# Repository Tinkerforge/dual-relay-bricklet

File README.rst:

Dual Relay Bricklet
===================

This repository contains the firmware source code and the hardware design
files. The documentation generator configs can be found at
https://github.com/Tinkerforge/generators

Repository Content
------------------

software/:
 * examples/: Examples for all supported languages
 * build/: Compiled files
 * src/: Source code of firmware
 * Makefile: Makefile to build project

hardware/:
 * Contains KiCad project files and additionally schematics as PDF

datasheets/:
 * Contains datasheets for sensors and complex ICs that are used

Hardware
--------

The hardware is designed with the open source EDA Suite KiCad
(http://www.kicad.org). Before you are able to open the files,
you have to install the Tinkerforge kicad-libraries
(https://github.com/Tinkerforge/kicad-libraries). You can either clone
them directly in hardware/ or clone them in a separate folder and
symlink them into hardware/
(ln -s kicad_path/kicad-libraries project_path/hardware). After that you
can open the .pro file in hardware/ with KiCad and from there view and
modify the schematics and the PCB layout.

Software
--------

If you want to do your own Brick/Bricklet firmware development we highly
recommend that you use our build environment setup script and read the
tutorial (https://www.tinkerforge.com/en/doc/Tutorials/Tutorial_Build_Environment/Tutorial.html).

To compile the C code we recommend you to install the newest GNU Arm Embedded
Toolchain (https://launchpad.net/gcc-arm-embedded/+download).
You also need to install bricklib (https://github.com/Tinkerforge/bricklib)
and brickletlib (https://github.com/Tinkerforge/brickletlib).

You can either clone it directly in software/src/ or clone it in a
separate folder and symlink it into software/src/
(ln -s bricklib_path/bricklib project_path/software/src/ and
ln -s brickletlib_path/brickletlib project_path/software/src/).
Finally make sure to have CMake installed
(http://www.cmake.org/cmake/resources/software.html).

After that you can build the firmware by invoking make in software/.
The firmware (.bin) can then be found in software/build/ and uploaded
with brickv (click button "Flashing" on start screen).

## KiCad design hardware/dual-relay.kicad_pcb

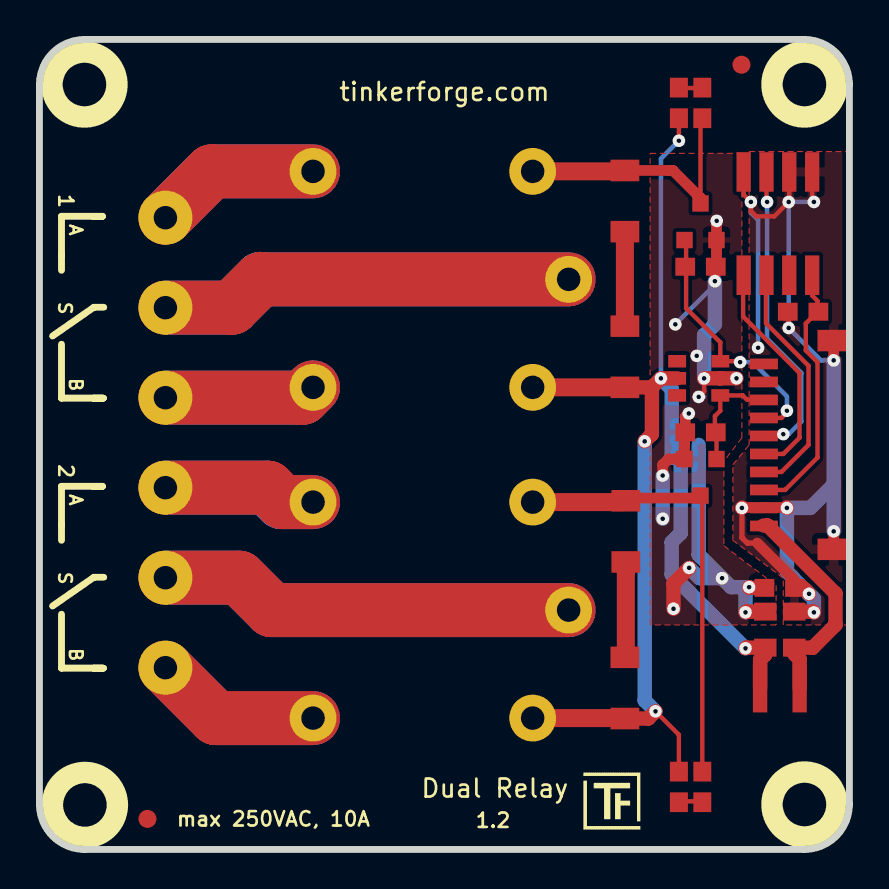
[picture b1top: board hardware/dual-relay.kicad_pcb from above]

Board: 2 copper layers, 45.0 x 45.0 mm, 34 parts (0 on the bottom side), 22 nets.

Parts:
C1, C3: 1µF; C0805
C2: 100nF; C0603E
D1, D2: LED blue; D0603E
D3, D5: 12V; MiniMelf
D4, D6: LL4148; MiniMelf
FB1: 4.7µH; NRH3015
FB2: 0R; C0603E
Fiducial_Mark: VAL**; Fiducial_Mark
Fiducial_Mark#2: VAL**; Fiducial_Mark
J1, J2, J3: AKL_5_2
P1: CON-SENSOR
Q1, Q2: 2N7002P; SOT23GDS
R1, R2, R3, R4: 1k; R0603E
Ref**: Val**; Logo_31x31
U1: M24C64; SO-8
U2, U3: ORWH-SX
U4: CM1293A; SC-74
U5, U6, U7, U8: DRILL; DRILL_NP
VAL: CE_5mm
VAL#2: WEEE_7mm

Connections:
+5V: C3.2, D1.1, D2.1, D3.1, D5.1, FB1.2, U2.1, U3.1, U4.5
AGND: C3.1, FB2.2, Q1.S, Q2.S, R1.1, R2.1, U4.2
GND: C1.1, C2.2, FB2.1, P1.2, P1.EP, U1.1, U1.2, U1.4
unnamed: C1.2, FB1.1, P1.1
unnamed: D1.2, R3.1
unnamed: D2.2, R4.1
unnamed: D3.2, D4.2
unnamed: D4.1, Q1.D, R3.2, U2.3
unnamed: D5.2, D6.2
unnamed: D6.1, Q2.D, R4.2, U3.3
unnamed: J1.1, U2.5
unnamed: J1.2, U2.2
unnamed: J2.1, U2.4
unnamed: J2.2, U3.5
unnamed: J3.1, U3.2
unnamed: J3.2, U3.4
unnamed: P1.6, U1.3
OUT1: P1.7, Q2.G, R2.2, U4.3
OUT2: P1.8, Q1.G, R1.2, U4.1
SCL: P1.4, U1.6
SDA: P1.5, U1.5
VCC: C2.1, P1.3, U1.8

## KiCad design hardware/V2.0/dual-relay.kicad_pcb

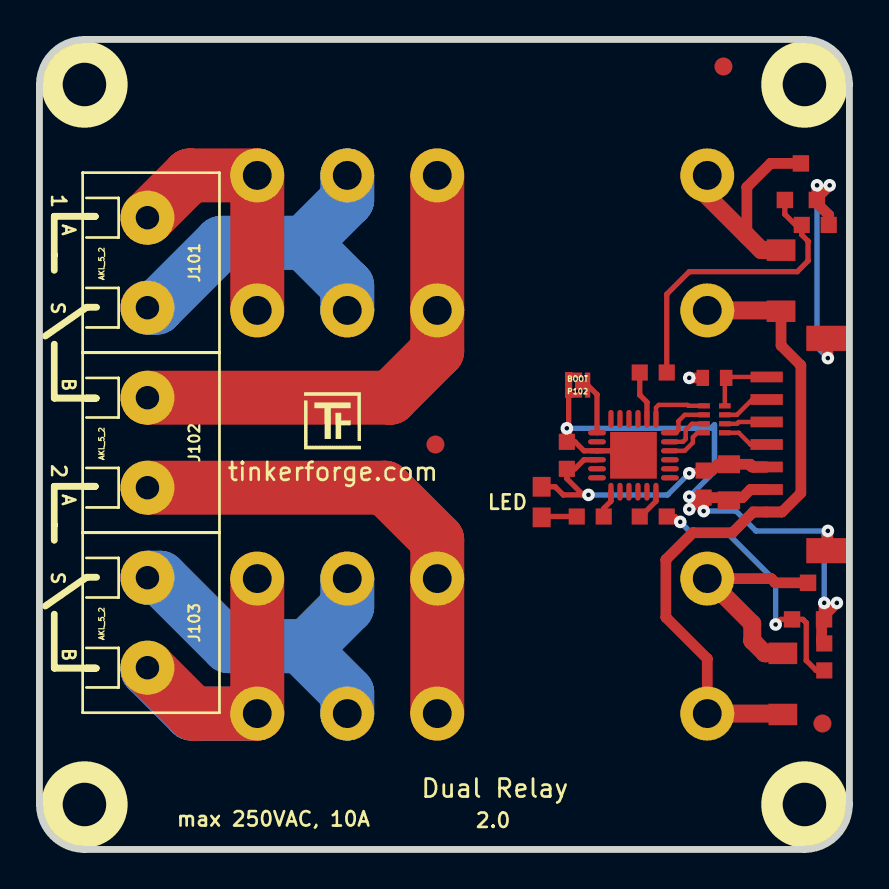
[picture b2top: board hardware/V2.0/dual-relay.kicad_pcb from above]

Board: 2 copper layers, 45.0 x 45.0 mm, 31 parts (0 on the bottom side), 26 nets.

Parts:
C101: 1uF; C0603F
C102: 1uF; C0402E
C103: 10uF; C0805
C104: 100nF; C0603F
D101: blue; D0603E
D102, D103: LL4148; MiniMelf
Fiducial_Mark: VAL**; Fiducial_Mark
Fiducial_Mark#2, Fiducial_Mark#3: VAL**; Fiducial_Mark
J101, J102, J103: AKL_5_2
P101: CON-SENSOR2
P102: BOOT; SolderJumper
Q101, Q102: 2N7002P; SOT23GDS
R101: 1k; R0603F
R102, R103: 10; R0603F
R104, R105: 10k; R0603F
REL101, REL102: RELAY_29_127
RP101: TBD; 4X0402
U101: XMC1XXX24; QFN24-4x4mm-0.5mm
U102, U103, U104, U105: DRILL; DRILL_NP
VAL: CE_5mm

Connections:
+5V: D102.2, D103.2, P101.1, REL101.A1, REL102.A1
GND: C101.1, C102.1, C103.1, C104.2, P101.2, P101.EP, P102.1, Q101.S, Q102.S, R104.1, R105.1, U101.9, U101.EXP
unnamed: C102.2, P101.7, RP101.4
unnamed: D101.2, R101.2
unnamed: D102.1, Q101.D, REL101.A2
unnamed: D103.1, Q102.D, REL102.A2
unnamed: J101.1, REL101.2, REL101.5
unnamed: J101.2, REL101.3, REL101.4
unnamed: J102.1, REL102.1, REL102.6
unnamed: J102.2, REL101.1, REL101.6
unnamed: J103.1, REL102.3, REL102.4
unnamed: J103.2, REL102.2, REL102.5
unnamed: P101.4, RP101.1
unnamed: P101.5, RP101.2
unnamed: P101.6, RP101.3
unnamed: P102.2, U101.7
unnamed: Q101.G, R102.1, R104.2
unnamed: Q102.G, R103.1, R105.2
unnamed: R101.1, U101.13
RELAY0: R103.2, U101.18
RELAY1: R102.2, U101.2
S-CLK: RP101.7, U101.23
S-CS: RP101.8, U101.22
S-MISO: RP101.5, U101.1
S-MOSI: RP101.6, U101.24
VCC: C101.2, C103.2, C104.1, D101.1, P101.3, U101.10

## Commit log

2011-08-25 initial hardware source commit
2011-08-25 add project description
2011-09-13 add java bindings and examples
2011-09-14 limit line length of java examples to 100 characters
2011-09-23 Add C# examples and bindings
2011-10-05 Remove Bindings and IP Connection (these are generated and they change too often) and rename bindings to examples
2011-10-05 add tinkerforge package to python imports
2011-10-06 remove faulty gcc commandline invocation
2011-10-06 add firmware version and name
2012-02-13 checkin of version V1.1 - remove resistor in address line - add fiducial markers - increase copper distances
2012-02-14 add compatability for different tick types
2012-02-15 Add changelog
2012-02-15 Move software changelog to software folder
2012-04-25 Unify capitalization of "IP connection" in examples
2012-05-09 Add PHP examples
2012-05-14 java: Remove unnecessary new String(...) calls
2012-05-25 Add Ruby example
2012-06-12 Use correct term 'Bricklet' in example code error message
2012-06-12 Prefer IPConnection destroy over join_thread
2012-06-30 Add monoflop functionality
2012-07-01 Add generate_makefile.bat for windows
2012-07-25 Add Delphi example
2012-08-08 delphi: Add comment about UID
2012-08-24 Add new datasheet
2012-10-24 Make cmake find the correct objcopy binary
    On some systems cmake uses the wrong objcopy binary, tell it to use
    the correct one.
2012-11-13 Support for protocol 2.0
2012-11-28 Make python examples protocol 2.0 compatible
2012-11-29 Make Ruby examples Protocol 2.0 compatible
2012-11-29 Make C examples Protocol 2.0 compatible
2012-11-29 Make Java examples Protocol 2.0 compatible
2012-11-29 Remove ipcon.destroy from java example
2012-11-29 Fix parameter order in com_return_error calls
2012-11-29 Make PHP examples Protocol 2.0 compatible
2012-11-29 Make Delphi/Pascal examples Protocol 2.0 compatible
2012-11-30 delphi: Remove unnecessary parentheses and call destructor again
2012-12-05 Add protocol 2.0 compatability to C# bindings
2013-01-14 Add possibility to set selected state to API
2013-02-07 Use IPconnection disconnect explicitly in examples
2013-02-18 Add Visual Basic .NET example
2013-08-09 Add shell example
2013-08-21 windows: Don't trigger a build in generate_makefile.bat
    Also use normal make instead of a special named one.
2013-12-29 checkin of new hardware files version 1.2
2014-01-06 Add static assert for BrickContext size
2014-01-08 delphi: Make example toggle the relays
2014-01-08 shell: Make example toggle the relays
2014-01-10 Add Perl examples
2014-01-15 php: Use const for constant values
2014-02-07 Add Mathematica examples
2014-02-10 perl: fixed namespace
2014-02-12 javascript: add examples
2014-02-18 javascript: examples fixed
2014-02-20 javascript: add html examples
2014-02-24 javascript: port 4280, startExample()
2014-02-28 javascript: Break long lines and cleanup whitespace
2014-03-05 Add LabVIEW example
2014-03-06 labview: Add example in LV2010 format
2014-03-25 matlab: add examples
2014-04-02 java: Unify constants style
2014-04-02 perl: Unify print style
2014-04-17 matlab: Remove \n prefix from input line
2014-04-17 matlab: Add parentheses to make pygments happy
2014-07-15 java: Replace System.console() usage with an Eclipse compatible pattern
2014-12-02 Use ReadLine instead of ReadKey for C# example
2015-02-13 vbnet: Use ReadLine instead of ReadKey
    Because ReadKey doesn't work with a pipe as stdin on the RED Brick.
2015-03-02 windows: Stop cmake from searching for mingw32-make.exe
    Using MinGW Makefiles as generator makes cmake search for mingw32-make.exe
    which might not be installed because GnuWin32's make.exe is used instead.
2015-04-09 c: Whitespace
2015-07-23 Make JavaScript browser example textarea readonly
2015-07-27 Cleanup C/C++, C#, Java, Python and Ruby examples
2015-07-29 Reformat changelog
2015-08-07 Use full device class name in Python example
2015-08-14 Cleanup Delphi example
2015-08-14 Fix minor warnings in C/C++ example
2015-08-18 Unify example loop logic
2015-08-18 Fix typo in C/C++ example
2015-08-18 Fix more typos in C/C++ example
2015-08-18 Cleanup VB.NET examples
2015-08-19 Cleanup Perl example
2015-09-09 Duplicate cmake call to fix bug during cmake creation
2015-10-08 Generator based example cleanup
2015-11-12 matlab: Fix callback handling for R2014a
    http://undocumentedmatlab.com/blog/matlab-callbacks-for-java-events-in-r2014a
2015-11-25 Include date and commit into changelog
2016-05-18 c: Add missing device destroy call
2016-06-17 change design for better production
2016-06-17 more improvements
2016-06-29 Whitespace
2016-07-01 Make the change UID comment more explicit
2017-04-28 prototype of new version
2017-05-04 change filtering to r/c circuit
2017-05-04 add fiducials, logos, protection diodes
2017-05-08 add description
2017-06-02 octave: Use javaObject instead of deprecated java_new
2017-11-27 Add 3d information (final)
2017-11-27 Add 3d model (*.step & *.FCStd)
2017-12-07 mathematica: Also generate .nb files
2018-01-26 c: Fine-tune define placement
2018-02-19 javascript: Close div tag correctly
2018-02-20 Cleanup KiCad libraries config
    Ensure LibDir=kicad-libraries and LibName1=tinkerforge.
    Remove special library.
2018-05-24 perl: Use strict in examples
2018-07-11 Add Makefile with docker support
2018-07-11 Update directory structure and build instructions
2018-07-11 Remove obsolete generate_makefile scripts
2018-11-06 Add rust examples
2018-11-07 rust: Accept host names for ip connection, fix naming inconsistencies
2018-12-14 Add go examples.
2018-12-18 go: Change import path.
2018-12-18 go: Change import path again.
2018-12-20 rust: Reformat examples.
2019-01-24 mqtt: Add examples.
2019-01-24 mqtt: Fix example header.
2019-01-24 mqtt: Remove executable bit in example permissions.
2019-01-24 go: Minor example fixes.
2019-01-24 mqtt: Minor example fixes.
2019-01-29 rust: Fix unused loop index.
2019-05-07 Don't clear monoflop time on monoflop abort to match documentation
2020-01-13 examples: Use python3 input instead of python2 raw_input.
2020-01-13 examples: mqtt: Remove trailing whitespace.
2020-03-23 mqtt: Update for loop style
2020-04-07 examples: rust: Always block when calling bindings functions.
2021-10-25 Update KiCad link
    https://www.kicad.org/blog/2021/10/Avoid-links-to-former-kicad-domain/
2022-07-06 Add license files.

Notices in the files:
hardware/V2.0/dual-relay.kicad_pcb:
Licensed under CERN OHL v.1.1
Copyright (©) 2017, B.Nordmeyer
Copyright Tinkerforge GmbH 2017.
This documentation describes Open Hardware and is licensed under the
CERN OHL v. 1.1.
hardware/dual-relay.kicad_pcb:
Copyright (©) 2013, B.Nordmeyer
Copyright Tinkerforge GmbH 2013.
